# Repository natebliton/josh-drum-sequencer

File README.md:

# josh-drum-sequencer
This is the code for a Daisy-based drum synth/sequencer for my friend Josh.

Look in the PegSequencer folder for the software, and in the kicad folder for the board design(s). There is also an ealrier draft of the code, and some other notes.

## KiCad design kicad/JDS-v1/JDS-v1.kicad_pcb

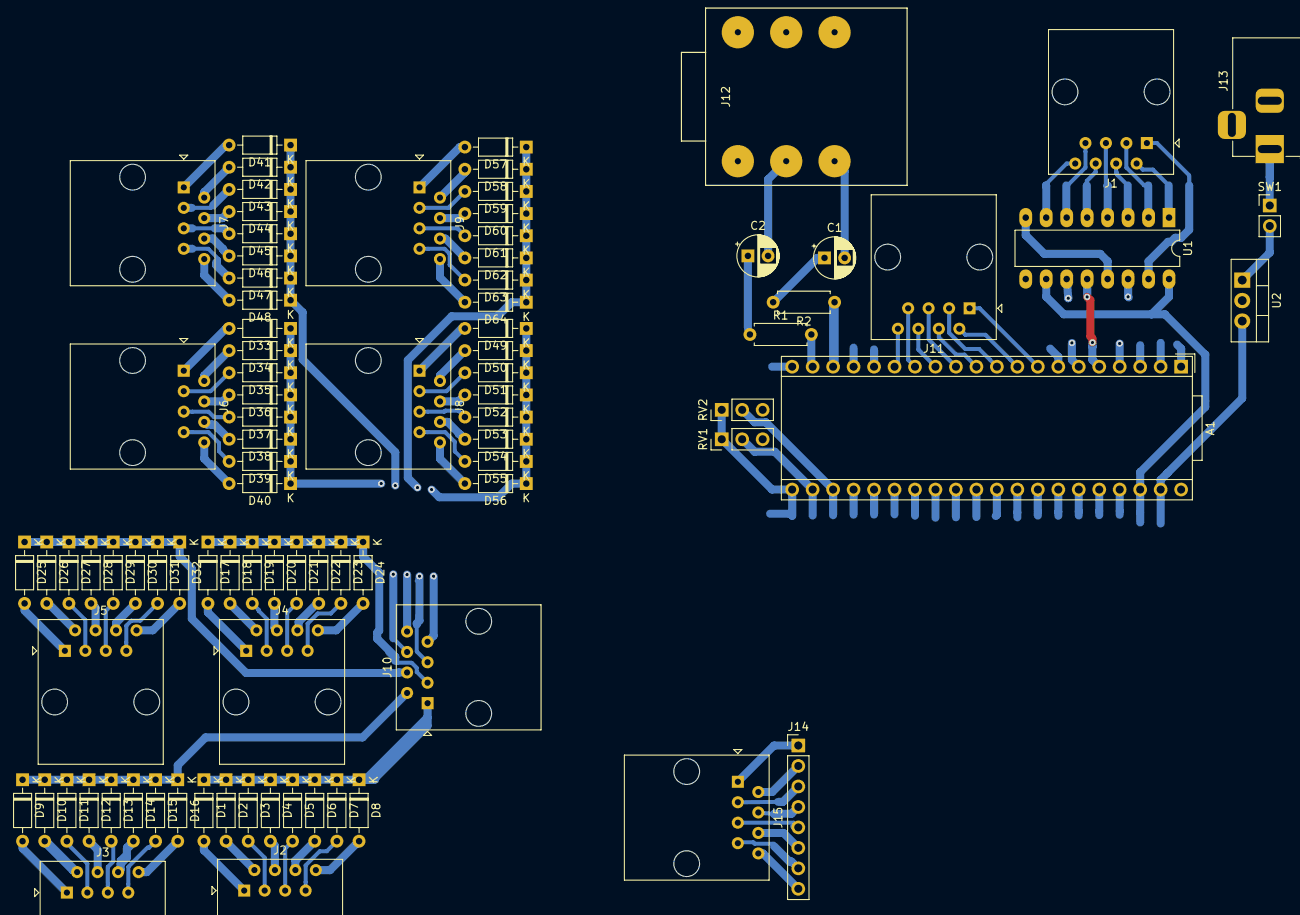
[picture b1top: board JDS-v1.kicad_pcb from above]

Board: 2 copper layers, 89 parts (0 on the bottom side), 113 nets.

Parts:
A1: Daisy; Device_Audio_Electrosmith_Daisy_Seed
C1, C2: 10uF; CP_Radial_D5.0mm_P2.50mm
D1, D2, D3, D4, D5, D6, D7, D8, D9, D10, D11, D12, D13, D14, D15, D16, D17, D18, D19, D20, D21, D22, D23, D24, D25, D26, D27, D28, D29, D30, D31, D32, D33, D34, D35, D36, D37, D38, D39, D40, D41, D42, D43, D44, D45, D46, D47, D48, D49, D50, D51, D52, D53, D54, D55, D56, D57, D58, D59, D60, D61, D62, D63, D64: 1N4148; D_DO-35_SOD27_P7.62mm_Horizontal
J1: toPegMatrix; RJ45_Amphenol_54602-x08_Horizontal
J2: fromPegsA; RJ45_Amphenol_54602-x08_Horizontal
J3: fromPegsB; RJ45_Amphenol_54602-x08_Horizontal
J4: fromPegsC; RJ45_Amphenol_54602-x08_Horizontal
J5: fromPegsD; RJ45_Amphenol_54602-x08_Horizontal
J6: fromPegsE; RJ45_Amphenol_54602-x08_Horizontal
J7: fromPegsF; RJ45_Amphenol_54602-x08_Horizontal
J8: fromPegsG; RJ45_Amphenol_54602-x08_Horizontal
J9: fromPegsH; RJ45_Amphenol_54602-x08_Horizontal
J10: mInJA; RJ45_Amphenol_54602-x08_Horizontal
J11: mInJB; RJ45_Amphenol_54602-x08_Horizontal
J12: Out; StereoJackTRS3
J13: Barrel_Jack_Switch; BarrelJack_Horizontal
J14: swOutJump; PinHeader_1x08_P2.54mm_Vertical
J15: swOut; RJ45_Amphenol_54602-x08_Horizontal
R1, R2: 100; R_Axial_DIN0207_L6.3mm_D2.5mm_P7.62mm_Horizontal
RV1: Vol; PinHeader_1x03_P2.54mm_Vertical
RV2: Tempo; PinHeader_1x03_P2.54mm_Vertical
SW1: POW-SW; PinHeader_1x02_P2.54mm_Vertical
U1: 74HC595; DIP-16_W7.62mm_LongPads
U2: LM7805_TO220; TO-220-3_Vertical

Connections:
+3.3VA: A1.21, RV1.1, RV2.1
+3V3: A1.38, U1.10, U1.16
+5V: A1.39, U2.3
GND: A1.40, J12.1, J13.2, RV1.3, RV2.3, U1.8, U1.13, U2.2
unnamed: A1.8, J11.1
unnamed: A1.9, J11.2
unnamed: A1.10, J11.3
unnamed: A1.11, J11.4
unnamed: A1.12, J11.5
unnamed: A1.13, J11.6
unnamed: A1.14, J11.7
unnamed: A1.15, J11.8
unnamed: C1.1, R2.2
unnamed: C1.2, J12.5
unnamed: C2.1, R1.1
unnamed: C2.2, J12.3
unnamed: D1.2, J2.1
unnamed: D2.2, J2.2
unnamed: D3.2, J2.3
unnamed: D4.2, J2.4
unnamed: D5.2, J2.5
unnamed: D6.2, J2.6
unnamed: D7.2, J2.7
unnamed: D8.2, J2.8
unnamed: D9.2, J3.1
unnamed: D10.2, J3.2
unnamed: D11.2, J3.3
unnamed: D12.2, J3.4
unnamed: D13.2, J3.5
unnamed: D14.2, J3.6
unnamed: D15.2, J3.7
unnamed: D16.2, J3.8
unnamed: D17.2, J4.1
unnamed: D18.2, J4.2
unnamed: D19.2, J4.3
unnamed: D20.2, J4.4
unnamed: D21.2, J4.5
unnamed: D22.2, J4.6
unnamed: D23.2, J4.7
unnamed: D24.2, J4.8
unnamed: D25.2, J5.1
unnamed: D26.2, J5.2
unnamed: D27.2, J5.3
unnamed: D28.2, J5.4
unnamed: D29.2, J5.5
unnamed: D30.2, J5.6
unnamed: D31.2, J5.7
unnamed: D32.2, J5.8
unnamed: D33.2, J6.1
unnamed: D34.2, J6.2
unnamed: D35.2, J6.3
unnamed: D36.2, J6.4
unnamed: D37.2, J6.5
unnamed: D38.2, J6.6
unnamed: D39.2, J6.7
unnamed: D40.2, J6.8
unnamed: D41.2, J7.1
unnamed: D42.2, J7.2
unnamed: D43.2, J7.3
unnamed: D44.2, J7.4
unnamed: D45.2, J7.5
unnamed: D46.2, J7.6
unnamed: D47.2, J7.7
unnamed: D48.2, J7.8
unnamed: D49.2, J8.1
unnamed: D50.2, J8.2
unnamed: D51.2, J8.3
unnamed: D52.2, J8.4
unnamed: D53.2, J8.5
unnamed: D54.2, J8.6
unnamed: D55.2, J8.7
unnamed: D56.2, J8.8
unnamed: D57.2, J9.1
unnamed: D58.2, J9.2
unnamed: D59.2, J9.3
unnamed: D60.2, J9.4
unnamed: D61.2, J9.5
unnamed: D62.2, J9.6
unnamed: D63.2, J9.7
unnamed: D64.2, J9.8
unnamed: J13.1, SW1.1
unnamed: J14.1, J15.1
unnamed: J14.2, J15.2
unnamed: J14.3, J15.3
unnamed: J14.4, J15.4
unnamed: J14.5, J15.5
unnamed: J14.6, J15.6
unnamed: J14.7, J15.7
unnamed: J14.8, J15.8
unnamed: SW1.2, U2.1
pm-clock: A1.4, U1.11
pm-enable: A1.5, U1.12
pm-in1: D1.1, D2.1, D3.1, D4.1, D5.1, D6.1, D7.1, D8.1, J10.1
pm-in2: D9.1, D10.1, D11.1, D12.1, D13.1, D14.1, D15.1, D16.1, J10.2
pm-in3: D17.1, D18.1, D19.1, D20.1, D21.1, D22.1, D23.1, D24.1, J10.3
pm-in4: D25.1, D26.1, D27.1, D28.1, D29.1, D30.1, D31.1, D32.1, J10.4
pm-in5: D33.1, D34.1, D35.1, D36.1, D37.1, D38.1, D39.1, D40.1, J10.5
pm-in6: D41.1, D42.1, D43.1, D44.1, D45.1, D46.1, D47.1, D48.1, J10.6
pm-in7: D49.1, D50.1, D51.1, D52.1, D53.1, D54.1, D55.1, D56.1, J10.7
pm-in8: D57.1, D58.1, D59.1, D60.1, D61.1, D62.1, D63.1, D64.1, J10.8
pm-out1: J1.1, U1.15
pm-out2: J1.2, U1.1
pm-out3: J1.3, U1.2
pm-out4: J1.4, U1.3
pm-out5: J1.5, U1.4
pm-out6: J1.6, U1.5
pm-out7: J1.7, U1.6
pm-out8: J1.8, U1.7
pm-serial: A1.6, U1.14
pot1: A1.22, RV1.2
pot2: A1.23, RV2.2
toAmpL: A1.18, R2.1
toAmpR: A1.19, R1.2

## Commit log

2021-07-14 updated gitignore to ignore DS_Store
2021-07-16 first test with drums sequencing combined example code from metro.cpp and Drum.cpp, step sequencer logic
2021-07-16 added shift register tutorial links
2021-07-16 initial kicad commit
2021-07-16 found kicad footprint link
2021-07-16 kicad iteration, found daisy footprint
2021-07-17 finished diode board and initial seed board
2021-07-17 iteration, and first print files
2021-07-19 fixed 595 shift register code
2021-07-19 deleted version with swapped 4 and 6 pins
2021-07-19 swapped 4 and 6 pins from seed to 595
2021-07-19 added shift register tutorial link
2021-07-23 added output buffer and first 9v-5v-3.3v power supply
2021-08-02 added tom1 and tom2 v1
2021-08-02 updated .gitignore to ignroe kicad backup files
2021-08-03 link for bubblegum sequencer
2021-08-03 changed connector footprints to RJ45
2021-08-03 added links for 3v schmitt trigger
2021-08-14 renamed shiftPins variable in ShiftOut
2021-08-14 added pots to schmatic and pcb
2021-08-14 started potentiometer programming
2021-08-14 added pots and extra traces, print v2
2021-08-15 added ethernet mounting PCBs and v3 print
2021-08-20 Added makefile to point to daisy libraries This allows for building binaries for this project as is
2021-08-20 added print of schematic
2021-08-20 added debugging flag
2021-08-20 added pin reading
2021-08-20 finished including libraries
2021-08-21 refactors to put shiftIn in a class
2021-08-21 started work on LED control
2021-10-04 replaced homebrew drums with Daisy objects
2021-12-22 rebased with stlink v3 debugger
2021-12-23 added snare, second higher kick, and hihat triggered by with test sequence
2021-12-23 added adc tempo knob and backstepped drums back to just kick and high kick, until more debugging
2022-01-20 tidy up, move earlier draft of code
2022-01-20 added windows 10 vscode config
2022-01-20 Moved ShiftOut class into own files
2022-01-20 put peg switches scanning into a for loop
